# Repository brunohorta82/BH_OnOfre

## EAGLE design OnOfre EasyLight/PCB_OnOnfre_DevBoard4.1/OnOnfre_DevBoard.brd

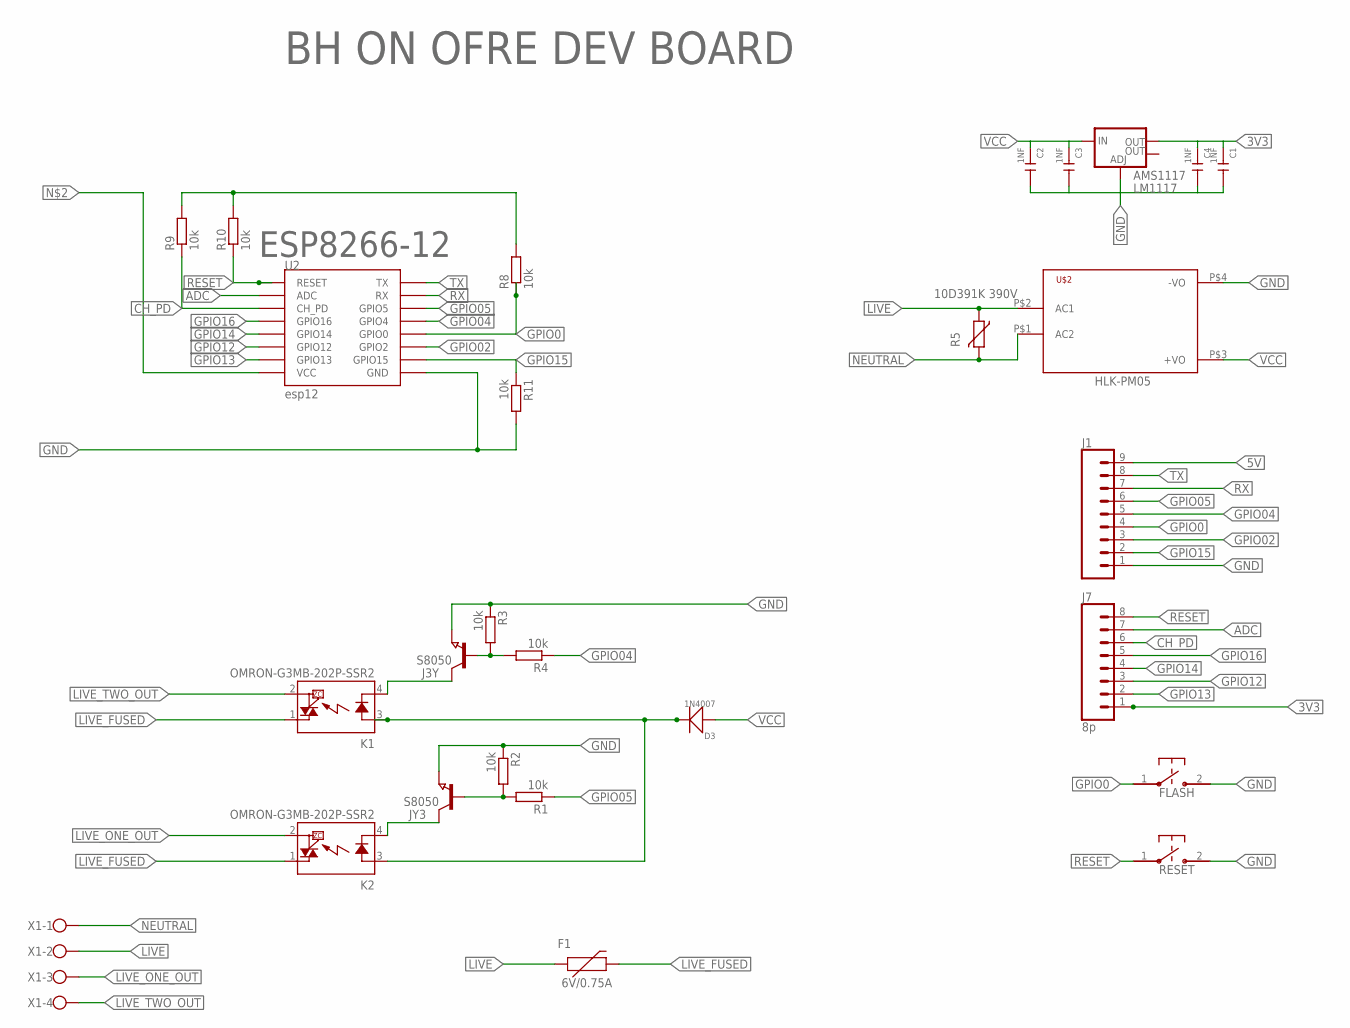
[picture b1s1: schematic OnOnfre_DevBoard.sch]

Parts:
AMS1117: LM1117; SOT223
C1, C2, C3, C4: 1NF; C1206
D3: 1N4007; DO-214AC
F1: 6V/0.75A; 1206
FLASH: B3U-1000P-2P-SMD; B3U-1000P
J1: CONN_09; 1X09
J3Y: S8050; SOT23
J7: 8p; 1X08
JY3: S8050; SOT23
K1, K2: OMRON-G3MB-202P-SSR2; OMRON-G3MB-202P-SSR
R1, R2, R3, R4, R8, R9, R10, R11: 10k; R0603
R5: 10D391K 390V; S07K230
RESET: B3U-1000P-2P-SMD; B3U-1000P
U2: esp12; ESP12-SMD
U$2: HKLPM01
X1: W237-4

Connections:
3V3: AMS1117.2 (OUT), C1.1, C4.1, J7.1, R8.2, R9.2, R10.2
5V: D3.2 (-), J1.9, K1.3 (A), K2.3 (A)
ADC: J7.7, U2.ADC
CH_PD: J7.6, R9.1, U2.CH_PD
GND: AMS1117.1 (ADJ), C1.2, C2.2, C3.2, C4.2, FLASH.2, J1.1, J3Y.2 (E), JY3.2 (E), R2.1, R3.1, R11.2, RESET.2, U2.GND, U$2.P$4 (-VO)
GPIO0: FLASH.1, J1.4, R8.1, U2.GPIO0
GPIO02: J1.3, U2.GPIO2
GPIO04: J1.5, R4.1, U2.GPIO4
GPIO05: J1.6, R1.1, U2.GPIO5
GPIO12: J7.3, U2.GPIO12
GPIO13: J7.2, U2.GPIO13
GPIO14: J7.4, U2.GPIO14
GPIO15: J1.2, R11.1, U2.GPIO15
GPIO16: J7.5, U2.GPIO16
LIVE: F1.1, R5.1, U$2.P$2 (AC1), X1.2
LIVE_FUSED: F1.2, K1.1 (DS1), K2.1 (DS1)
LIVE_ONE_OUT: K2.2 (DS2), X1.3
LIVE_TWO_OUT: K1.2 (DS2), X1.4
unnamed: J3Y.3 (C), K1.4 (K)
unnamed: J3Y.1 (B), R3.2, R4.2
unnamed: JY3.3 (C), K2.4 (K)
unnamed: JY3.1 (B), R1.2, R2.2
NEUTRAL: R5.2, U$2.P$1 (AC2), X1.1
RESET: J7.8, R10.1, RESET.1, U2.RESET
RX: J1.7, U2.RXD0 (RX)
TX: J1.8, U2.TXD0 (TX)
VCC: AMS1117.3 (IN), C2.1, C3.1, D3.1 (+), U$2.P$3 (+VO)

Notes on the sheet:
HLK-PM05
BH ON OFRE DEV BOARD
ESP8266-12

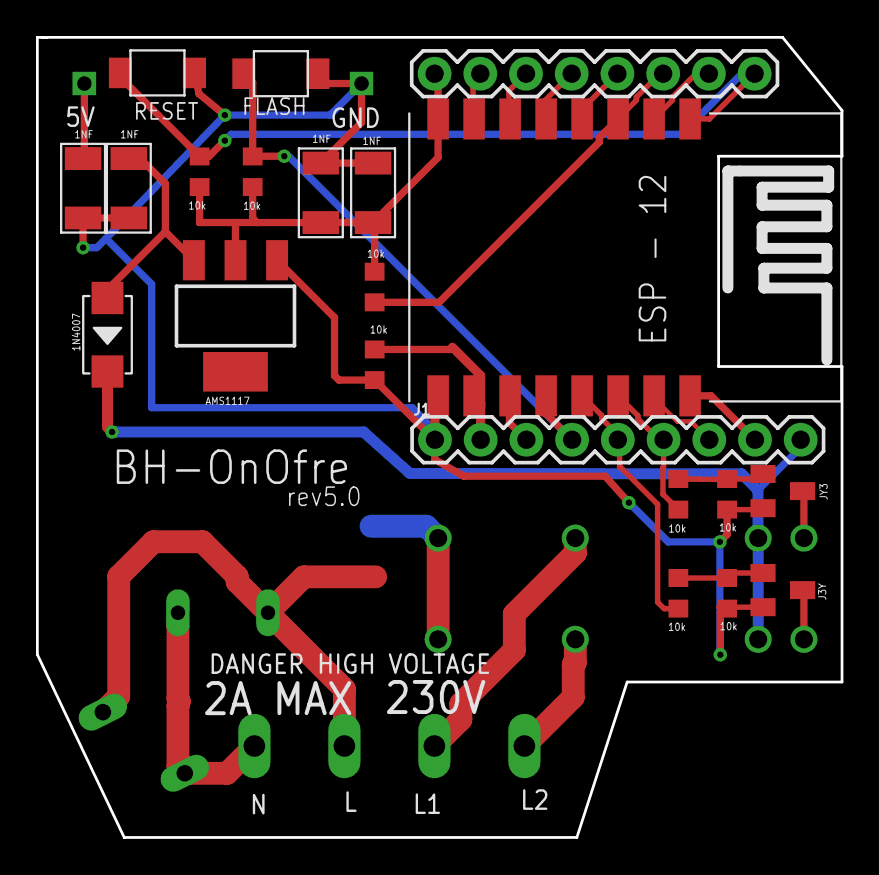
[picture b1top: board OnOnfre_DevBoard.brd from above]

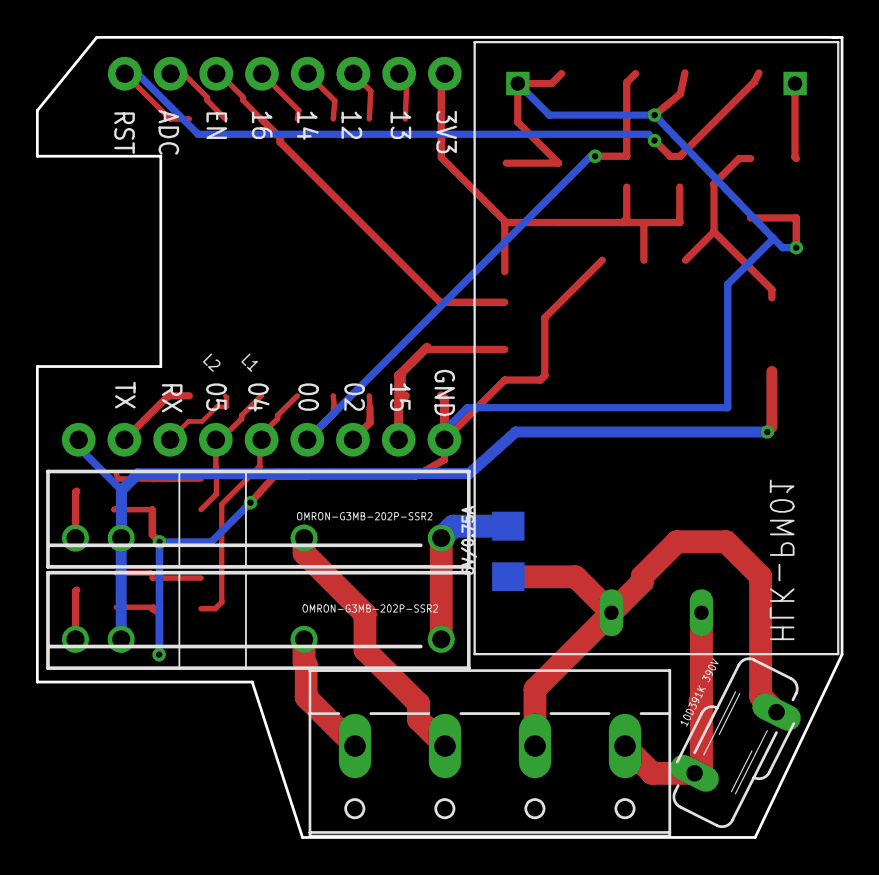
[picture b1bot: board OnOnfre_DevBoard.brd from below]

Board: 2 copper layers, 44.7 x 44.5 mm, 27 parts (5 on the bottom side), 27 nets.

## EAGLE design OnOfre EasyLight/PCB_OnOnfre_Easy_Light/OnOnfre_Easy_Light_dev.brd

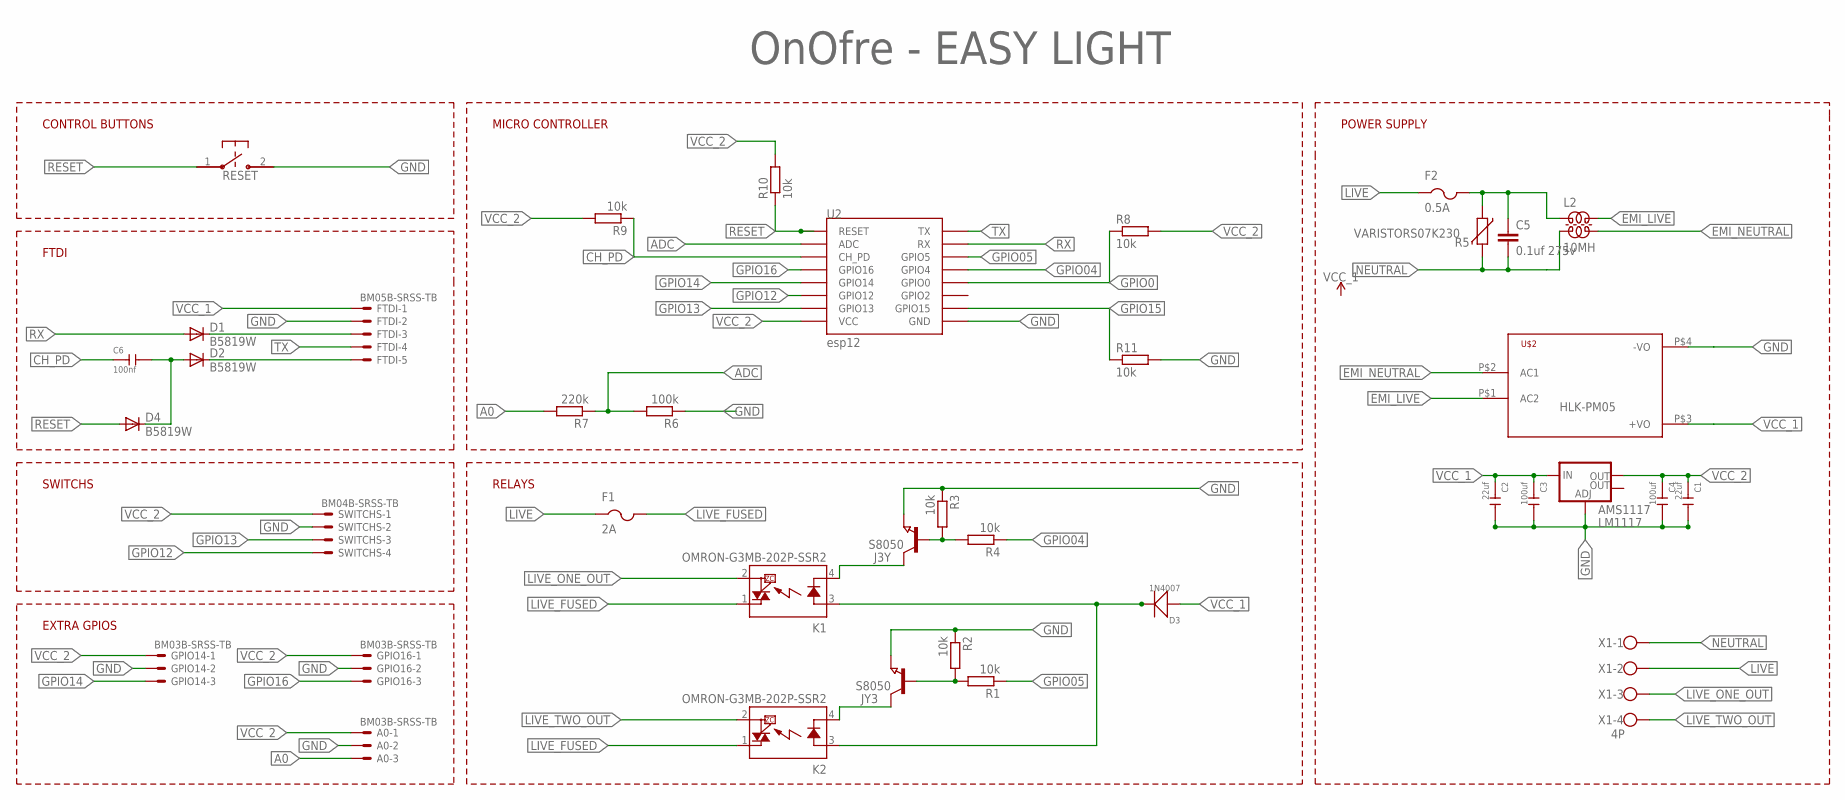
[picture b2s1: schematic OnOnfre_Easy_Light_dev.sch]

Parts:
A0: BM03B-SRSS-TB
AMS1117: LM1117; SOT223
C1, C2: 22uf; C1206
C3, C4: 100uf; C1206
C5: 0.1uf 275v; C102-054X133
C6: 100nf; C0603
D1, D2, D4: B5819W; SOD323-R
D3: 1N4007; DO-214AC
F1: 2A; 1812
F2: 0.5A; 1812
FTDI: BM05B-SRSS-TB
GPIO14, GPIO16: BM03B-SRSS-TB
J3Y: S8050; SOT23
JY3: S8050; SOT23
K1, K2: OMRON-G3MB-202P-SSR2; OMRON-G3MB-202P-SSR
L2: 10MH; ZD6-2X15
R1, R2, R3, R4, R8, R9, R10, R11: 10k; R0603
R5: VARISTORS07K230; S07K230
R6: 100k; R0603
R7: 220k; R0603
RESET: B3U-1000P-2P-SMD; B3U-1000P
SWITCHS: BM04B-SRSS-TB
U2: esp12; ESP12-SMD
U$2: HKLPM01
X1: 4P; W237-4

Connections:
5V: D3.2 (-), K1.3 (A), K2.3 (A)
A0: A0.3, R7.2
ADC: R6.2, R7.1, U2.ADC
CH_PD: C6.1, R9.1, U2.CH_PD
DTR: D2.C, FTDI.5
EMI_LIVE: L2.1 (4), U$2.P$1 (AC2)
EMI_NEUTRAL: L2.2 (3), U$2.P$2 (AC1)
GND: A0.2, AMS1117.1 (ADJ), C1.2, C2.2, C3.2, C4.2, FTDI.2, GPIO14.2, GPIO16.2, J3Y.2 (E), JY3.2 (E), R2.1, R3.1, R6.1, R11.2, RESET.2, SWITCHS.2, U2.GND, U$2.P$4 (-VO)
GPIO0: R8.1, U2.GPIO0
GPIO04: R4.1, U2.GPIO4
GPIO05: R1.1, U2.GPIO5
GPIO12: SWITCHS.4, U2.GPIO12
GPIO13: SWITCHS.3, U2.GPIO13
GPIO14: GPIO14.3, U2.GPIO14
GPIO15: R11.1, U2.GPIO15
GPIO16: GPIO16.3, U2.GPIO16
LIVE: F1.1, F2.1, X1.2
LIVE_FUSED: F1.2, K1.1 (DS1), K2.1 (DS1)
LIVE_ONE_OUT: K1.2 (DS2), X1.3
LIVE_TWO_OUT: K2.2 (DS2), X1.4
unnamed: J3Y.3 (C), K1.4 (K)
unnamed: C5.1, F2.2, L2.4 (1), R5.2
unnamed: D1.C, FTDI.3
unnamed: C6.2, D2.A, D4.C
unnamed: J3Y.1 (B), R3.2, R4.2
unnamed: JY3.3 (C), K2.4 (K)
unnamed: JY3.1 (B), R1.2, R2.2
NEUTRAL: C5.2, L2.3 (2), R5.1, X1.1
RESET: D4.A, R10.1, RESET.1, U2.RESET
RX: D1.A, U2.RXD0 (RX)
TX: FTDI.4, U2.TXD0 (TX)
VCC_1: AMS1117.3 (IN), C2.1, C3.1, D3.1 (+), FTDI.1, U$2.P$3 (+VO)
VCC_2: A0.1, AMS1117.2 (OUT), C1.1, C4.1, GPIO14.1, GPIO16.1, R8.2, R9.2, R10.2, SWITCHS.1, U2.VCC

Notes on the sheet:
HLK-PM05
POWER SUPPLY
MICRO CONTROLLER
RELAYS
CONTROL BUTTONS
FTDI
SWITCHS
OnOfre - EASY LIGHT
EXTRA GPIOS

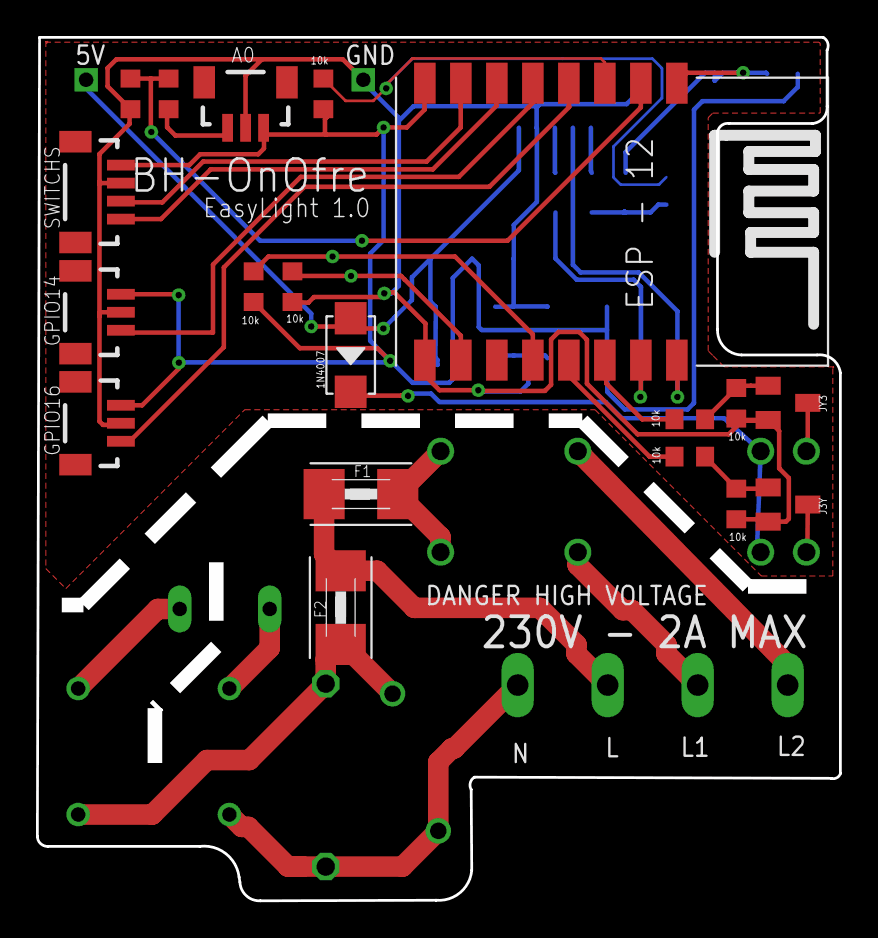
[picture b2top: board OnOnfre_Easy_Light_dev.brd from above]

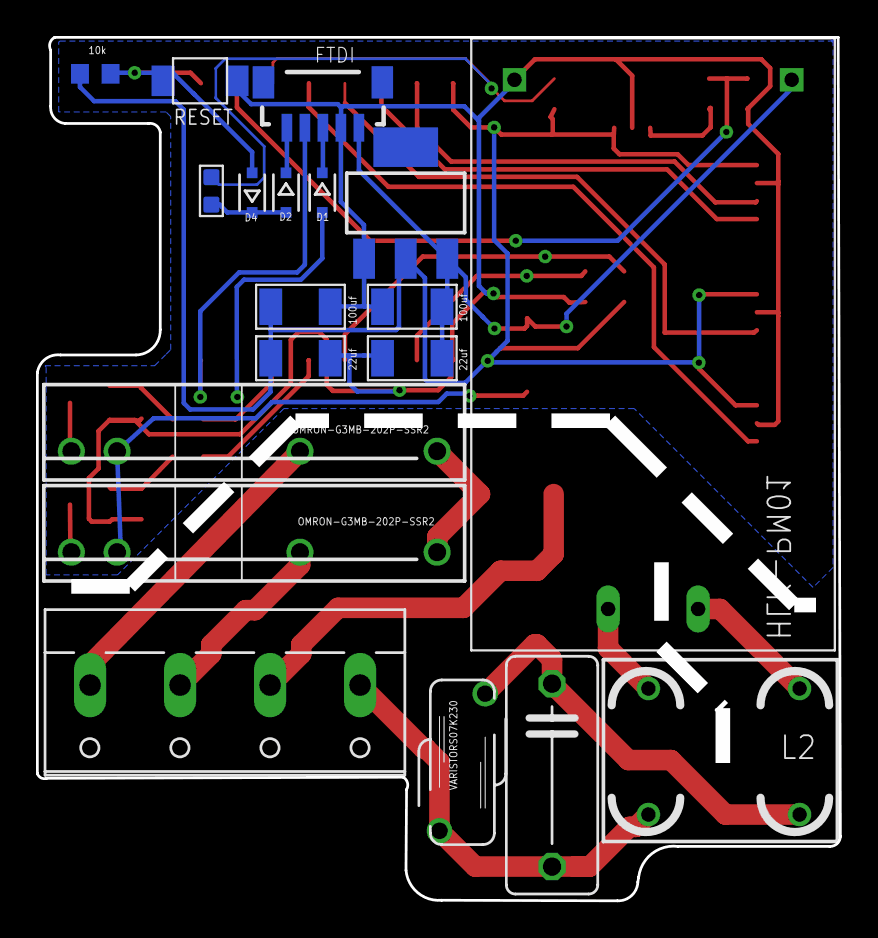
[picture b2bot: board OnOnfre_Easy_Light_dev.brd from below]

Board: 2 copper layers, 44.6 x 48.0 mm, 38 parts (18 on the bottom side), 33 nets.

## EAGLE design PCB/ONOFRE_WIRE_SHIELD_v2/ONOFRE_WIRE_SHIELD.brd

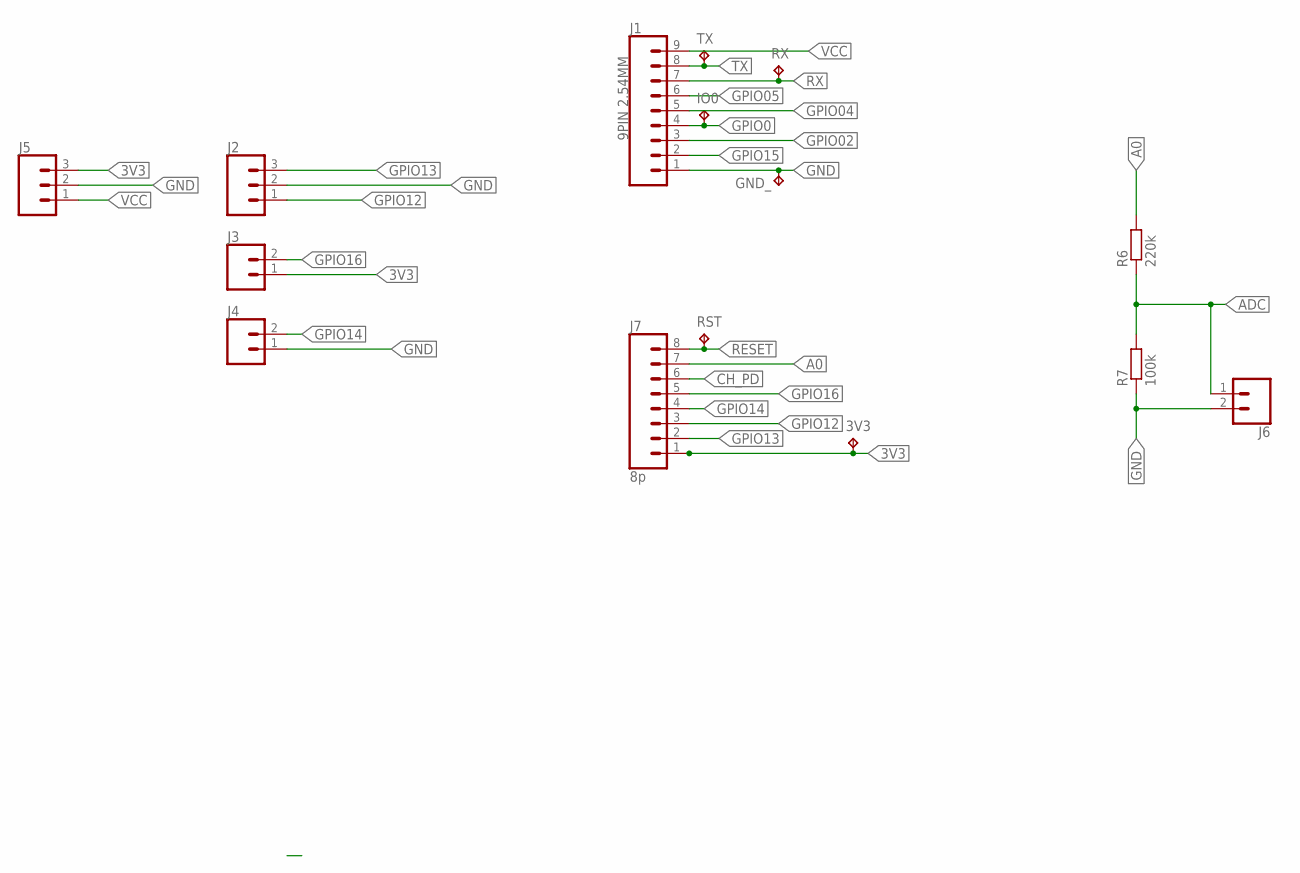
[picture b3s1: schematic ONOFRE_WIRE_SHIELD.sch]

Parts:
3V3: TPB1,27; B1,27
GND_: TPB1,27; B1,27
IO0: TPB1,27; B1,27
J1: 9PIN 2.54MM; 1X09
J2, J5: CONN_03; 1X03
J3, J4, J6: CONN_02; 1X02
J7: 8p; 1X08
R6: 220k; R0603
R7: 100k; R0603
RST: TPB1,27; B1,27
RX: TPB1,27; B1,27
TX: TPB1,27; B1,27

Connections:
3V3: 3V3.TP, J3.1, J5.3, J7.1
A0: J7.7, R6.2
ADC: J6.1, R6.1, R7.2
CH_PD: J7.6
GND: GND_.TP, J1.1, J2.2, J4.1, J5.2, J6.2, R7.1
GPIO0: IO0.TP, J1.4
GPIO02: J1.3
GPIO04: J1.5
GPIO05: J1.6
GPIO12: J2.1, J7.3
GPIO13: J2.3, J7.2
GPIO14: J4.2, J7.4
GPIO15: J1.2
GPIO16: J3.2, J7.5
RESET: J7.8, RST.TP
RX: J1.7, RX.TP
TX: J1.8, TX.TP
VCC: J1.9, J5.1

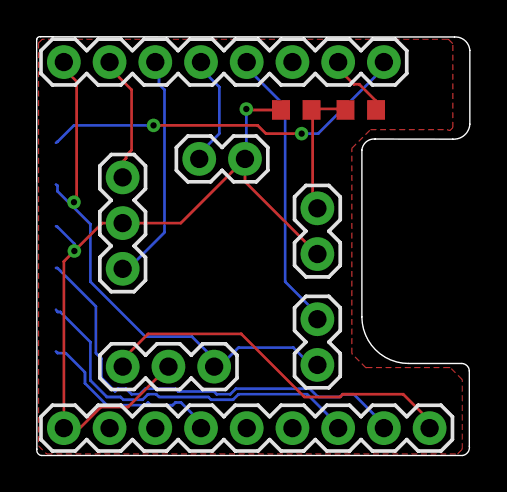
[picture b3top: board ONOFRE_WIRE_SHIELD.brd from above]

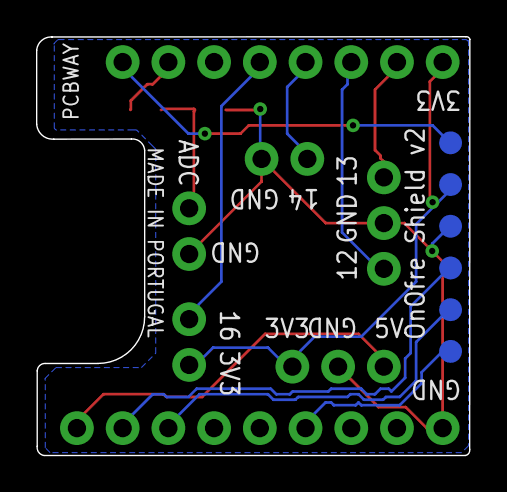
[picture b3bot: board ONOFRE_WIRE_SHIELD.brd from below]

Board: 2 copper layers, 24.1 x 23.3 mm, 15 parts (6 on the bottom side), 13 nets.

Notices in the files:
parts and their libraries:
SparkFun-Connectors: Licensing: Creative Commons ShareAlike 4.0 International - https://creativecommons.org/licenses/by-sa/4.0
